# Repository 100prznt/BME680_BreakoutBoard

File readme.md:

# BME680 Breakoutboard

### Schematic

* [Schematic_BME680_Breakout.pdf](Schematic_BME680_Breakout.pdf)

### Layout

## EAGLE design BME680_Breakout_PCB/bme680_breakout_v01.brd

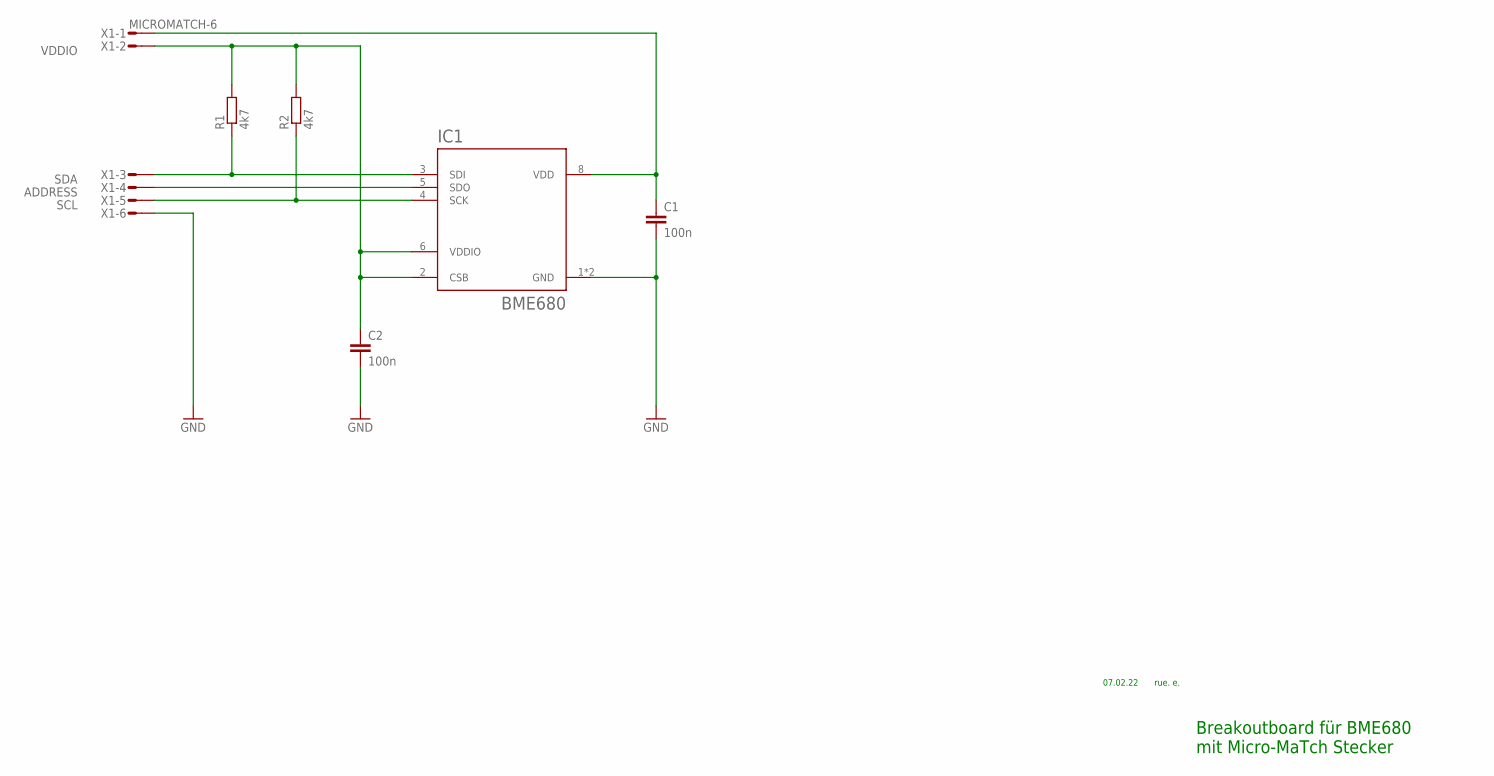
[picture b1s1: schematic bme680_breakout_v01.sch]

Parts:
C1, C2: 100n; C0805K
IC1: BME680; LGA8
R1, R2: 4k7; R0603
X1: MICROMATCH-6

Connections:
ADDRESS: IC1.5 (SDO), X1.4
GND: C1.2, C2.2, IC1.1 (GND), IC1.7 (GND), X1.6
SCL: IC1.4 (SCK), R2.1, X1.5
SDA: IC1.3 (SDI), R1.1, X1.3
VDD: C1.1, IC1.8 (VDD), X1.1
VDDIO: C2.1, IC1.2 (CSB), IC1.6 (VDDIO), R1.2, R2.2, X1.2

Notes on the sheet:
Breakoutboard für BME680 mit Micro-MaTch Stecker
rue. e.
07.02.22

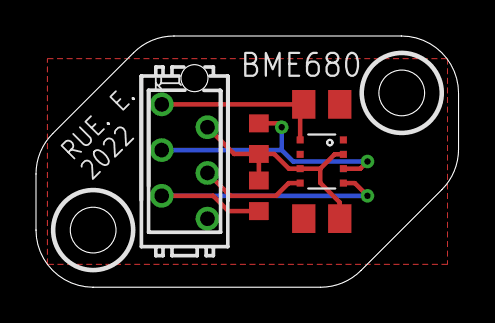
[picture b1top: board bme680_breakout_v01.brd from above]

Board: 2 copper layers, 23.5 x 14.0 mm, 6 parts (0 on the bottom side), 6 nets.

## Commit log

2022-02-07 Add eagle prj
2022-02-07 change pcb color
